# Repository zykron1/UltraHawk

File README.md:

# UltraHawk
A custom fully autonomous drone designed to run custom firmware on a fully custom flight controller. It is capable of autonomously navigating to waypoints.

Ultrahawk utilizes a fully custom PCB made out of SMT components that can be manufactured via a pick-and-place machine, or manually soldered on via hot plate.
You may find KiCAD files in the pcb directory, along with the production folder including a .zip file for easy export to PCB services as JLCPCB and PCBWay.
Components may be found in the `bom.csv` file containing the LCSC part numbers for each part.

UltraHawk also uses a custom frame that is designed to be 3D printed. CAD files for this can be found in the `CAD` folder as `.step` files.

The drone can then be assembled using the rest of the parts such as motors, esc's, and batteries, all of which can be found in the `bom.csv` file.
Perliminary firmware for the project may also be found in the `firmware` directory.

See bom.csv for full price breakdown.
See JOURNAL.md for full work log.

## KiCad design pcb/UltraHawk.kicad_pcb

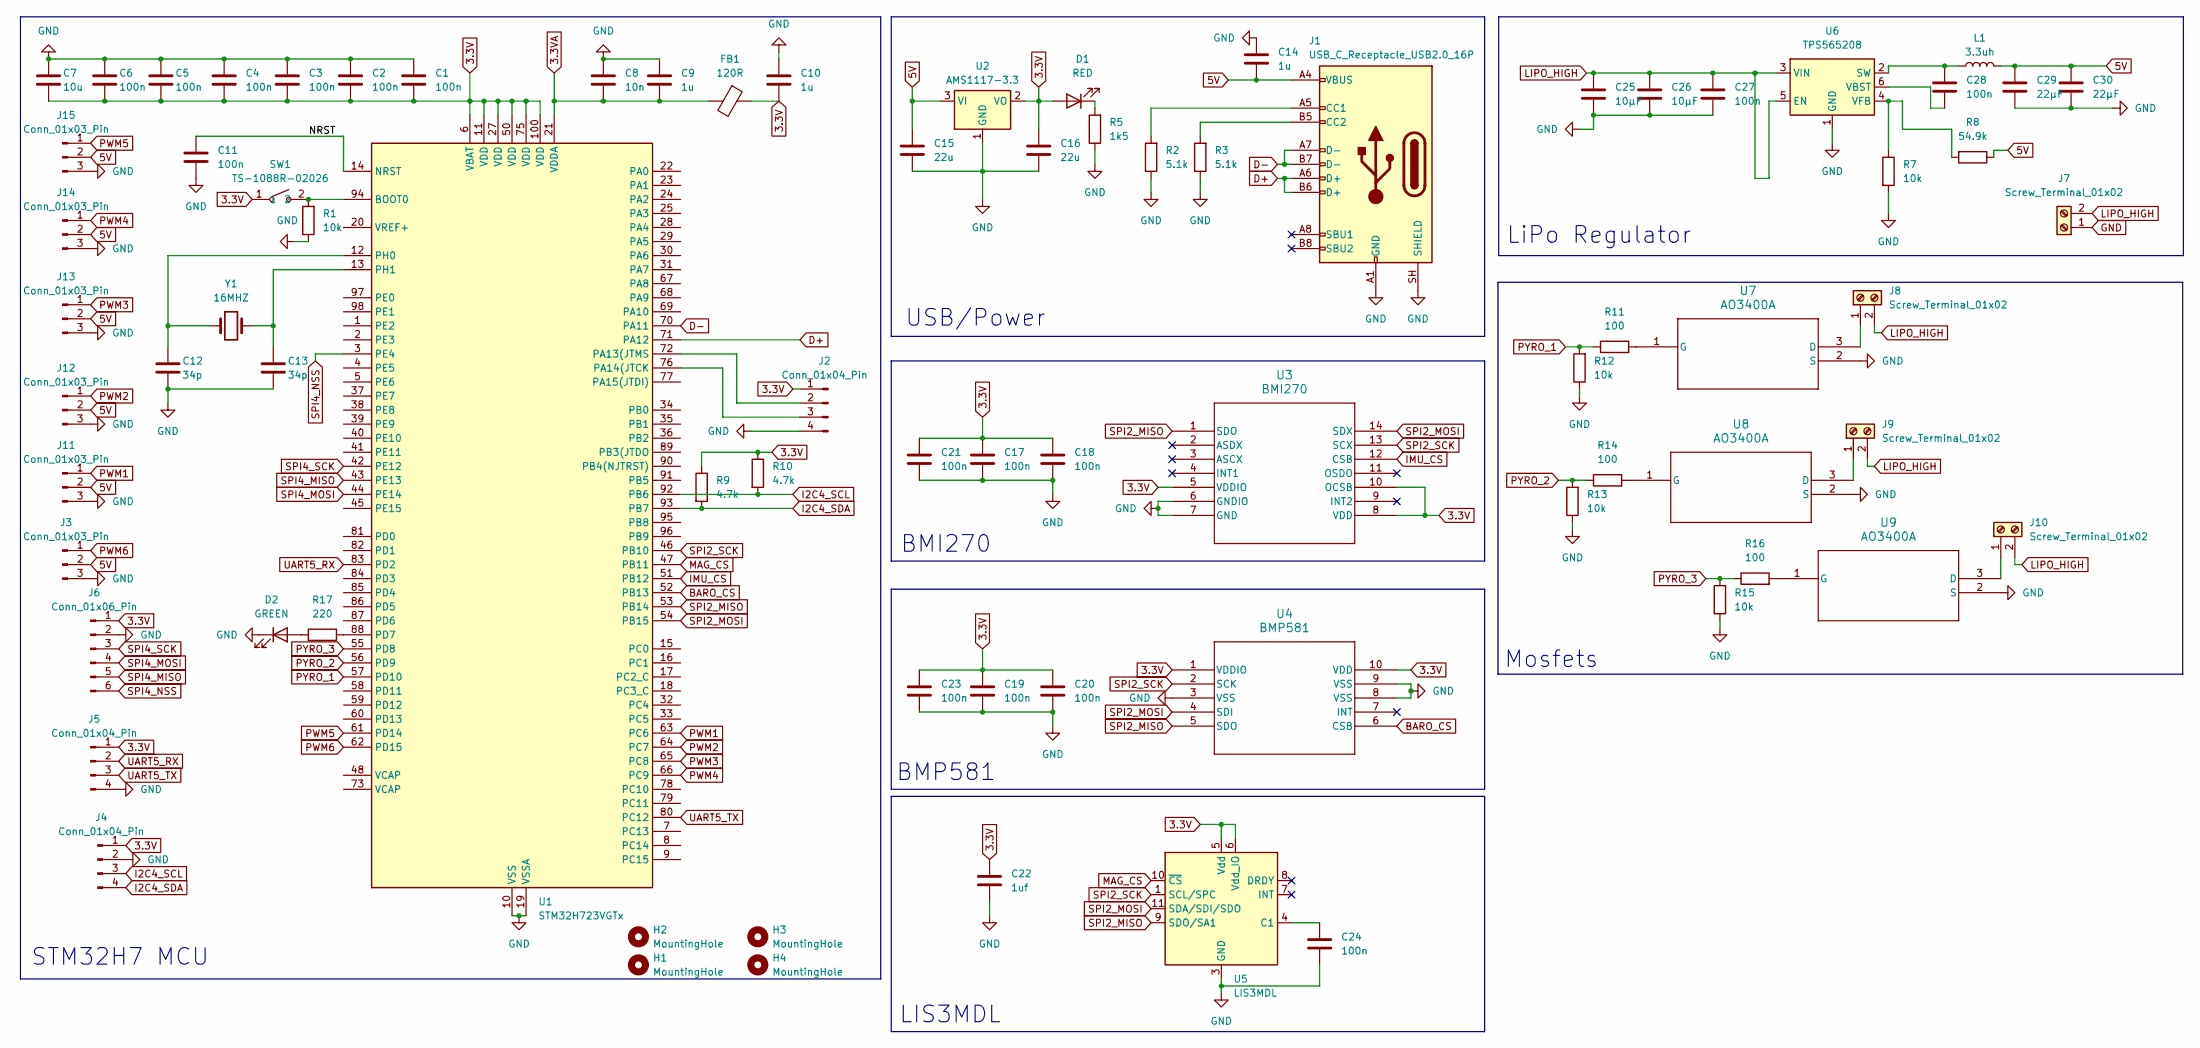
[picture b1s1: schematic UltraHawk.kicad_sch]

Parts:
C1, C2, C3, C4, C5, C6, C11, C17, C18, C19, C20, C21, C23, C24, C27, C28: 100n; C_0805_2012Metric
C7: 10u; C_0805_2012Metric
C8: 10n; C_0805_2012Metric
C9, C10, C14: 1u; C_0805_2012Metric
C12, C13: 34p; C_0805_2012Metric
C15, C16: 22u; C_0805_2012Metric
C22: 1uf; C_0805_2012Metric
C25, C26: 10µF; C_0805_2012Metric
C29, C30: 22µF; C_0805_2012Metric
D1: RED; LED_0805_2012Metric
D2: GREEN; LED_0805_2012Metric
FB1: 120R; R_0603_1608Metric_Pad0.98x0.95mm_HandSolder
H1, H2, H3, H4: MountingHole; MountingHole_3.2mm_M3
J1: USB_C_Receptacle_USB2.0_16P; USB_C_Receptacle_GCT_USB4105-xx-A_16P_TopMnt_Horizontal
J2, J4, J5: Conn_01x04_Pin; PinHeader_1x04_P2.54mm_Vertical
J3, J11, J12, J13, J14, J15: Conn_01x03_Pin; PinHeader_1x03_P2.54mm_Vertical
J6: Conn_01x06_Pin; PinHeader_1x06_P2.54mm_Vertical
J7, J8, J9, J10: Screw_Terminal_01x02; TerminalBlock_MaiXu_MX126-5.0-02P_1x02_P5.00mm
L1: 3.3uh; IND-SMD_L5.8-W5.2
R1, R7, R12, R13, R15: 10k; R_0805_2012Metric
R2, R3: 5.1k; R_0805_2012Metric
R5: 1k5; R_0805_2012Metric
R8: 54.9k; R_0805_2012Metric
R9, R10: 4.7k; R_0805_2012Metric
R11, R14, R16: 100; R_0805_2012Metric
R17: 220; R_0805_2012Metric
SW1: TS-1088R-02026; SW-SMD_L3.9-W3.0-P4.45; LCSC Part C455280
U1: STM32H723VGTx; LQFP-100_14x14mm_P0.5mm
U2: AMS1117-3.3; SOT-223-3_TabPin2
U3: BMI270; BMI270_BOS
U4: BMP581; QFN10_BMP581_BOS
U5: LIS3MDL; LGA-12_2x2mm_P0.5mm
U6: TPS565208; SOT-23-6
U7, U8, U9: AO3400A; SOT-23-3L_AOS
Y1: 16MHZ; Crystal_HC49-U_Vertical

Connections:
3.3V: C1.2, C2.2, C3.2, C4.2, C5.2, C6.2, C7.2, C10.2, C16.1, C17.1, C18.1, C19.1, C20.1, C21.1, C22.1, C23.1, D1.2 (A), FB1.1, J2.1, J4.1, J5.1, J6.1, R9.1, R10.1, SW1.1, U1.6 (VBAT), U1.11 (VDD), U1.27 (VDD), U1.50 (VDD), U1.75 (VDD), U1.100 (VDD), U2.2 (VO), U3.5 (VDDIO), U3.8 (VDD), U3.10 (OCSB), U4.1 (VDDIO), U4.10 (VDD), U5.5 (Vdd), U5.6 (Vdd_IO); also elsewhere on the board
3.3VA: C8.2, C9.2, FB1.2, U1.21 (VDDA)
5V: C14.2, C15.1, C29.1, C30.1, J1.A4 (VBUS), J1.A9 (VBUS), J1.B4 (VBUS), J1.B9 (VBUS), J3.2, J11.2, J12.2, J13.2, J14.2, J15.2, L1.1, R8.1, U2.3 (VI)
/NRST: C11.1, U1.14 (NRST)
BARO_CS: U1.52 (PB13), U4.6 (CSB)
D+: J1.A6 (D+), J1.B6 (D+), U1.71 (PA12)
D-: J1.A7 (D-), J1.B7 (D-), U1.70 (PA11)
GND: C1.1, C2.1, C3.1, C4.1, C5.1, C6.1, C7.1, C8.1, C9.1, C10.1, C11.2, C12.2, C13.2, C14.1, C15.2, C16.2, C17.2, C18.2, C19.2, C20.2, C21.2, C22.2, C23.2, C24.2, C25.2, C26.2, C27.2, C29.2, C30.2, D2.1 (K), J1.A1 (GND), J1.A12 (GND), J1.B1 (GND), J1.B12 (GND), J1.SH (SHIELD), J2.4, J3.3, J4.2, J5.4, J6.2, J7.1, J11.3, J12.3, J13.3, J14.3, J15.3, R1.1, R2.1, R3.1, R5.1, R7.2, R12.1, R13.1, R15.1, U1.10 (VSS), U1.19 (VSSA), U1.26 (VSS), U1.49 (VSS), U1.74 (VSS), U1.99 (VSS), U2.1 (GND), U3.6 (GNDIO), U3.7 (GND), U4.3 (VSS), U4.8 (VSS), U4.9 (VSS), U5.2 (GND), U5.3 (GND), U5.12 (GND), U6.1 (GND), U7.2 (S), U8.2 (S), U9.2 (S); also elsewhere on the board
I2C4_SCL: J4.3, R10.2, U1.92 (PB6)
I2C4_SDA: J4.4, R9.2, U1.93 (PB7)
IMU_CS: U1.51 (PB12), U3.12 (CSB)
LIPO_HIGH: C25.1, C26.1, C27.1, J7.2, J8.2, J9.2, J10.2, U6.3 (VIN), U6.5 (EN); also elsewhere on the board
MAG_CS: U1.47 (PB11), U5.10 (~CS)
unnamed: D1.1 (K), R5.2
unnamed: D2.2 (A), R17.1
unnamed: J1.A5 (CC1), R2.2
unnamed: J1.B5 (CC2), R3.2
unnamed: J2.2, U1.72 (PA13(JTMS)
unnamed: J2.3, U1.76 (PA14(JTCK)
unnamed: J8.1, U7.3 (D)
unnamed: J9.1, U8.3 (D)
unnamed: J10.1, U9.3 (D)
unnamed: R1.2, SW1.2, U1.94 (BOOT0)
unnamed: R17.2, U1.88 (PD7)
unnamed: C12.1, U1.12 (PH0), Y1.1
unnamed: C13.1, U1.13 (PH1), Y1.2
unnamed: C24.1, U5.4 (C1)
unnamed: C28.1, L1.2, U6.2 (SW)
unnamed: C28.2, U6.6 (VBST)
unnamed: R7.1, R8.2, U6.4 (VFB)
unnamed: R11.2, U7.1 (G)
unnamed: R14.2, U8.1 (G)
unnamed: R16.2, U9.1 (G)
PWM1: J11.1, U1.63 (PC6)
PWM2: J12.1, U1.64 (PC7)
PWM3: J13.1, U1.65 (PC8)
PWM4: J14.1, U1.66 (PC9)
PWM5: J15.1, U1.61 (PD14)
PWM6: J3.1, U1.62 (PD15)
PYRO_1: R11.1, R12.2, U1.57 (PD10)
PYRO_2: R13.2, R14.1, U1.56 (PD9)
PYRO_3: R15.2, R16.1, U1.55 (PD8)
SPI2_MISO: U1.53 (PB14), U3.1 (SDO), U4.5 (SDO), U5.9 (SDO/SA1)
SPI2_MOSI: U1.54 (PB15), U3.14 (SDX), U4.4 (SDI), U5.11 (SDA/SDI/SDO)
SPI2_SCK: U1.46 (PB10), U3.13 (SCX), U4.2 (SCK), U5.1 (SCL/SPC)
SPI4_MISO: J6.5, U1.43 (PE13)
SPI4_MOSI: J6.4, U1.44 (PE14)
SPI4_NSS: J6.6, U1.3 (PE4)
SPI4_SCK: J6.3, U1.42 (PE12)
UART5_RX: J5.2, U1.83 (PD2)
UART5_TX: J5.3, U1.80 (PC12)

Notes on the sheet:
USB/Power
BMI270
LiPo Regulator
BMP581
Mosfets
STM32H7 MCU
LIS3MDL

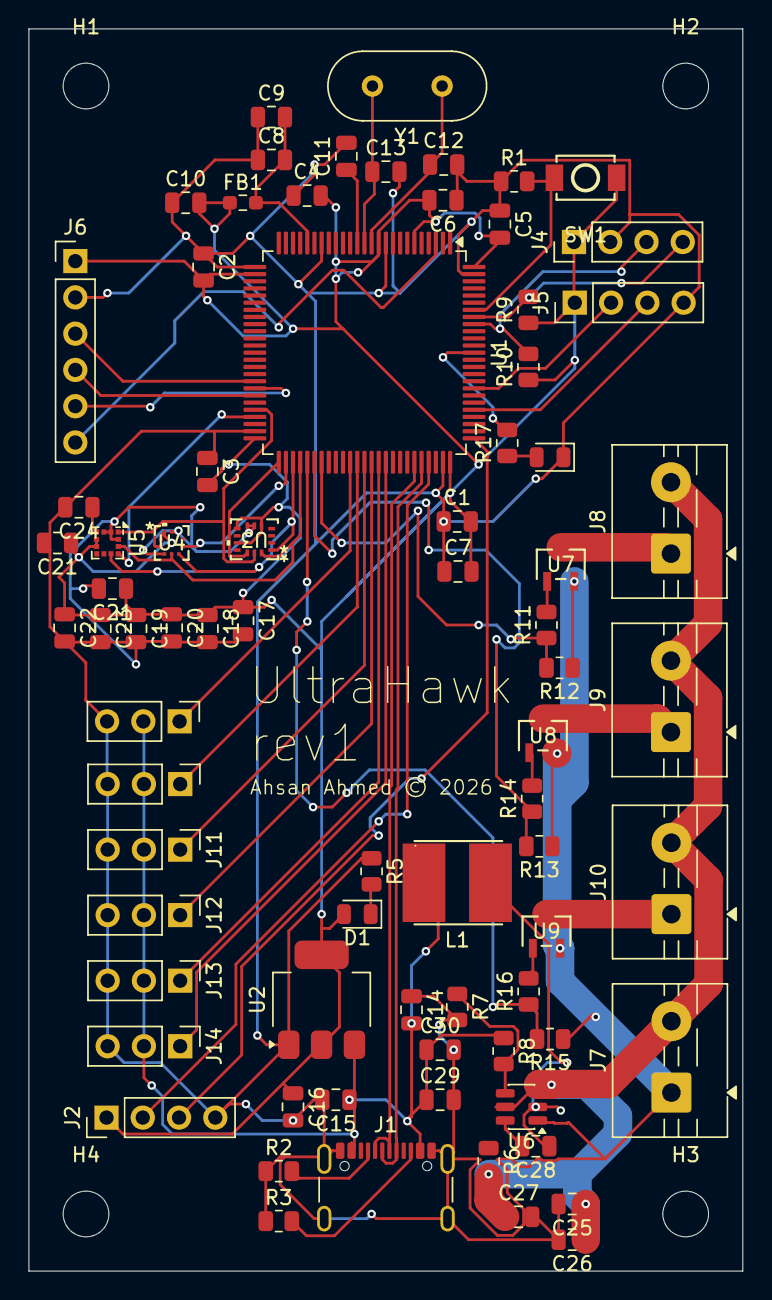
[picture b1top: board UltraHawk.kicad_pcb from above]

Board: 2 copper layers, 50.0 x 87.0 mm, 81 parts (0 on the bottom side), 51 nets.

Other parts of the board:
C21#2: 100n; C_0805_2012Metric
R6: 10k; R_0805_2012Metric

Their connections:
3.3V: C21#2.1; also elsewhere on the board
GND: C21#2.2; also elsewhere on the board
LIPO_HIGH: R6.2; also elsewhere on the board

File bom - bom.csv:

Designator,Footprint,Quantity,Value,LCSC Part #,Cost Per Unit,Cost,Note,
"C1, C11, C17, C18, C19, C2, C20, C21_2, C21, C23, C24, C3, C4, C5, C6, C27, C28",805,17,100n,C344180,$0.02,$0.35,Multiples of 10,
"C10, C14, C9",805,3,1u,C24123,$0.0195,$0.39,moq 20,
"C12, C13",805,2,34p,C3894194,$0.0017,$0.09,moq 50,
"C15, C16",805,2,22u,C602037,$0.1138,$1.14,moq 10,
C22,805,1,1uf,C28323,$0.0469,$0.94,moq 20,
"C25, C26",805,2,10µF,C1713,$0.0491,$0.98,moq 20,
"C29, C30",805,2,22µF,C5674,$0.07,$0.70,moq 10,
C7,805,1,10u,C17024,$0.04,$0.84,moq 20,
C8,805,1,10n,C1710,$0.01,$0.47,moq 50,
D1,805,1,RED,C84256,$0.01,$0.67,moq 50,
D2,805,1,GREEN,C5879267,$0.42,$0.42,no moq,
FB1,603,1,120R,C14709,$0.01,$0.74,moq 50,
J1,USB_C_Receptacle_GCT_USB4105-xx-A_16P_TopMnt_Horizontal,1,USB_C_Receptacle_USB2.0_16P,C5184243,$1.17,$1.17,no moq,
"J10, J7, J8, J9",TerminalBlock_MaiXu_MX126-5.0-02P_1x02_P5.00mm,4,Screw_Terminal_01x02,C5188434,$0.06,$0.62,moq 10,
"J11, J12, J13, J14, J15, J3",PinHeader_1x03_P2.54mm_Vertical,6,Conn_01x03_Pin,C2337,$0.16,$0.78,moq 5,
"J2, J4, J5",PinHeader_1x04_P2.54mm_Vertical,3,Conn_01x04_Pin,sharing from above,sharing from above,0,sharing from above,
J6,PinHeader_1x06_P2.54mm_Vertical,1,Conn_01x06_Pin,sharing from above,sharing from above,0,sharing from above,
L1,805,1,3.3uh,C18734461,$0.02,$0.12,moq 5,
"R1, R12, R13, R15, R6, R7",805,6,10k,C84376,$0.00,$0.38,moq 100,Factory ded
"R10, R9",805,2,4.7k,C4176634,$0.01,$0.01,no moq,Factory ded
"R11, R14, R16",805,3,100,C2907218,$0.00,$0.32,moq 100,Factory ded
R17,805,1,220,C104105,$0.00,$0.26,,
"R2, R3",805,2,5.1k,C2930296,$0.00,$0.22,moq 100,
R5,805,1,1k5,C416128,$0.00,$0.26,moq 100,
R8,805,1,54.9k,C137510,$0.00,$0.28,moq 100,Factory ded
SW1,SW-SMD_L3.9-W3.0-P4.45,1,TS-1088R-02026,C455280,$0.06,$0.60,moq 5,
U1,LQFP-100_14x14mm_P0.5mm,1,STM32H723VGTx,C730142,$6.99,$6.99,no moq,
U2,SOT-223-3_TabPin2,1,AMS1117-3.3,C6186,$0.20,$0.99,moq 5,
U3,BMI270_BOS,1,BMI270,C2836813,$4.15,$4.15,no moq,
U4,QFN10_BMP581_BOS,1,BMP581,C5362283,$4.31,$4.31,no moq,
U5,LGA-12_2x2mm_P0.5mm,1,LIS3MDL,C478483,$5.04,$5.04,no moq,
U6,SOT-23-6,1,TPS565208,C2650336,$0.44,$0.44,no moq,
"U7, U8, U9",SOT-23-3L_AOS,3,AO3400A,C20917,$0.08,$0.42,moq 5,
Y1,Crystal_HC49-U_Vertical,1,16MHZ,C326538,$0.53,$0.53,no moq,
,,,,,,$35.63,,
Name,Cost,Link,,,,,,
JLCPCB Stencil+PCB+Shipping,$18.87,n/a,,,,,,
BLDC + ESC + Props,$55.99,https://www.amazon.com/gp/product/B0BW5H7Y8Q/,,,,,,
OVONIC 3S Lipo Battery 50C 5200mAh,$25.54,https://www.amazon.com/5200mAh-Battery-Connector-Airplane-He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,,,,,,
LCSC Total(SEE LCSC.CSV!!!),$35.63,n/a,,,,,,
LCSC Shipping,$20,estimate,,,,,,
,$156.03,,,,,,,

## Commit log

2026-06-15 Create initial JOURNAL.md file
2026-06-16 Journal Update #1
2026-06-17 Journal Update #2
2026-06-17 Journal Update #3
2026-06-17 images
2026-06-17 fix images
2026-06-17 Fix typos and improve grammar in JOURNAL.md
    Corrected spelling and grammatical errors throughout the journal entries for clarity and readability.
2026-06-17 Journal Update #4
2026-06-18 Pcb layout
2026-06-18 fixes
2026-06-18 Journal Update #5
2026-06-18 image
2026-06-18 Grammar
2026-06-18 Include PCB images in README
    Add images of the PCB to the README.
2026-06-18 silkscreen
2026-06-18 DRC fixes
2026-06-20 Journal Update
2026-06-21 CAD Writeup
2026-06-21 CAD sync'
2026-06-21 Add image of drone to README
2026-06-22 firmware perliminary
2026-06-22 readme
2026-06-22 README.md updates to fit hcb rubric
2026-06-29 Telemetry firmware
2026-06-29 two way datalink support
2026-06-29 dumb bug
2026-06-30 PID Hover
2026-06-30 MMU operational

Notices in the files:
pcb/UltraHawk.kicad_pcb:
Ahsan Ahmed © 2026
